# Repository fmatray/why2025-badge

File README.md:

# WHY2025 Badge

The Cyber Saiyan community designed and developed a special gadget to celebrate [WHY2025](https://www.cybersaiyan.it/why2025/)... You can get one of the 200 available badges at the [Cyber Saiyan Village](https://wiki.why2025.org/Village:Cyber_Saiyan) and start playing.

## Useful information:

* To play with and hack the badge, we recommend bringing a **USB Type‑C data cable**
* The badge is already flashed with the WHY2025 specific firmware
* We would greatly appreciate any improvements to the project and pull requests.
* Don't hesitate to come and visit us at the Cyber Saiyan Village if you need help
* **Bonus**: on [Day 2, Aug 9, 2025 at 16:00 in Cassiopeia](https://cfp.why2025.org/why2025/talk/3CSQRF/) we present the hardware design and the firmware during the talk "Summoning Shenron: Building the Cyber Saiyan Badge"

## Features

The badge has several simple features to enhance your Village experience:
* It is designed to recall the dragon spheres (maybe you will be able to summon Shenron...)
* The core is a low-power **ESP32-C3** SoC
   * Integrates a 32-bit single-core RISC-V microcontroller with a maximum clock speed of 160 MHz
   * 400 KB of internal RAM and 4MB flash
   * Wi-Fi and Bluetooth 5 (LE)
   * 16 programmable GPIOs
* In the front there are 7 RGB leds
* In the back you have  
   * A 2.8'' TFT screen 
   * A LiPo battery, connectors and power switch
   * A reset button
   * 2 Dial Wheel Switch
   * 8 connectors for configurable GPIOs and expansions

## Interaction

Once powered on, the badge is assigned an ID from 1 to 7 and begins advertising itself via BLE.

**Change Screens**: **Long-press** (at least 1 second) either Dial Wheel Switch.

You can interact with the screen by short pressing (up or down) one of the two Dial Wheel Switch.

## Screens

### First screen

The Cyber Saiyan WHY2025 logo

### Second screen

A BADGE with a name, an organization, a job and a message... and a secret identity ;-)

### Thrid screen

The Cyber Saiyan Village schedule. Use the 5th screen to update it.

### Fourth Screen

The badge radar, showing nearby badges in a Dragon Ball style.

### Fifth screen

The badge's list, you can see all the badges around in a table view

### Sixt screen

The Wi-Fi functionalities

#### TURN ON AP

Start the AP mode (move up the Dial Wheel Switch) and connect from your PC/phone to the badge AP using SSID and PASS shown; after that you can navigate to `http://192.168.4.1` in order to explore more functionalities (hey Harry, can you play tetris?) and change configurations (`saiyan` is the pwd)

#### SYNC SCHEDULE

Start the SYNC mode (move down the Dial Wheel Switch) in order to update the Village schedule; the badge connects to WHY2025 open wi-fi to download the updated schedule from Cyber Saiyan website

### Seventh Screen
Have fun while playing Snake! 🐍

## Characteristics

The ESP32-C3 chip is the MCU at the core of the WHY2025 Badge, it integrates multiple peripherals to enable communication with the outside world.
The number of available pins is limited to keep the chip package size small. To route all the incoming and outgoing signals a set of software programmable registers controls the pin multiplexer.

### Peripheral Interfaces
There are 16 programmable GPIO pins available for:
* Digital interfaces
   * 3 SPI
   * 2 UART
   * I2C
   * I2S
   * Remote control peripheral, with 2 transmit channels and 2 receive channels
   * LED PWM controller, with up to 6 channels
   * Full-speed USB Serial/JTAG controller
   * General DMA controller (GDMA), with 3 transmit channels and 3 receive channels
   * TWAI® controller compatible with ISO 11898-1 (CAN Specification 2.0)
* Analog interfaces
   * 2 SAR ADCs (12-bit), up to 6 channels
   * Temperature sensor

### Devices on board
The WHY2025 Badge is equipped with a 2.8 inch TFT color LCD screen with 240 x 320 pixels, using the [ST7789](hardware/datasheet/ST7789V.pdf) display controller.
This display integrates a resistive touchscreen a white LEDs backlight and features an 18-pin standard FPC cable to interface the MCU with a 4-wire SPI bus.
___
The SPI bus signals are available on the connector labeled "SPI" at the top of the badge:
| pin  | function |
| :--- | :------: |
| 1    |   GND    |
| 2    |   MOSI   |
| 3    |    CS    |
| 4    |    DC    |
| 5    |   CLK    |
| 6    |   MISO   |

___
The current firmware version does not support touchscreen functionality, but the Badge still features the [TSC2007](hardware/datasheet/tsc2007.pdf) I2C Resistive Touch Screen Controller.

The front RGB LEDs are intelligent, individually addressable [WS2812B](hardware/datasheet/WS2812B.pdf) chips that communicate with each other and the microcontroller via a single data line. The data transfer protocol uses a single NZR communication mode. The signal from the DOUT port of the last LED on the badge is available on the "1W" pin of the connector, labeled "I2C."
___
The I2C bus signals are available on the connector labeled "I2C" at the top of the badge:
| pin  | function |
| :--- | :------: |
| 1    |   GND    |
| 2    |   SCL    |
| 3    |   SDA    |
| 4    |    1W    |
___
The display backlight is controlled by 4 pins on the [AW9523B](hardware/datasheet/AW9523.pdf) LED driver and GPIO controller with I2C interface while the other 12 pins on the I/O ports can be configured as LED drive mode or GPIO mode and are available on the connector labeled "RGB*".
___
The I/O signals from AW9523B are available on the connector labeled "RGB*" at the left of the badge:
| RGB0 | function |
| :--- | :------: |
| 1    |   GND    |
| 2    |   P0_0   |
| 3    |   P0_1   |
| 4    |   P0_2   |

| RGB1 | function |
| :--- | :------: |
| 1    |   GND    |
| 2    |   P0_3   |
| 3    |   P0_4   |
| 4    |   P0_5   |

| RGB2 | function |
| :--- | :------: |
| 1    |   GND    |
| 2    |   P0_6   |
| 3    |   P0_7   |
| 4    |   P1_4   |

| RGB3 | function |
| :--- | :------: |
| 1    |   GND    |
| 2    |   P1_5   |
| 3    |   P1_6   |
| 4    |   P1_7   |
___

The badge's main input interface consists of two **Dial Wheel Switches**. These switches can be rotated up or down for short and long presses to navigate and interact with the UI.
Pressing the center of the left switch results in the same effect as rotating the wheel UP, while pressing the center of the right switch results in the same effect as rotating the wheel DOWN.

Note: 
push the left switch (or rotating the wheel UP) during boot to put the MCU in Joint Download Boot mode to download binary files into flash using UART0 or USB interface. To reset/restart the MCU push the micro switch labeled "RST" on the top left of the badege.

During the boot process, the messages by the ROM code can be printed to (Default) UART0 and USB Serial/JTAG controller. 
___
The UART interface and the Strapping (button pin) signals are available on the connector labeled "RS232" at the top of the badge:
| pin  | function |
| :--- | :------: |
| 1    |   GND    |
| 2    |    TX    |
| 3    |    RX    |
| 4    | button B |
| 5    | button A |

___

The USB-C connector's D+/D- pins are connected to the default USB Serial/JTAG Controller and the USB power is routed to the LiPo battery charger and the voltage regulators.

There is the [MT3608](hardware/datasheet/MT3608B.pdf) step-up converter intended for power the WS2812 with up to 5V and the [MT3410LB](hardware/datasheet/MT3410LB-N.pdf) step-down DC-DC 3.3V regulator, capable of delivering up to 1.3A output current to the MCU and all the other IC.

In case of low power and low noise applications it's possible to disable the MT3410LB by removing two 0 ohm resistors labeled SW_ON/SW_OUT and enable the [RT9080](hardware/datasheet/RT9080-33.pdf) low-dropout (LDO) 3.3 voltage regulator by shorting two resistors pads labeled LDO_ON/LDO_OUT
___
The power lines are available on the connector labeled "POW" at the top of the badge:
| pin  | function |
| :--- | :------: |
| 1    |   GND    |
| 2    |  +3.3V   |
| 3    |  +4.75V  |
___

The battery is charged using a [TP4054](hardware/datasheet/TP4054.pdf) single-charge LiPo charger with a constant current/voltage algorithm and a [DW01](hardware/datasheet/dw01a.pdf) protection IC designed to protect the battery from damage due to over-discharge and/or over-current. The charging circuit and voltage regulators are always powered by the USB port. A toggle switch for turning the badge on and off via the battery is located on the bottom of the badge.

# Toolchain setup

## Prepare the environment 

### Visual Studio Code (VSCode)
Install Visual Studio Code as development environment:

* https://code.visualstudio.com/ - follow instructions there, if you don't have vscode yet.

### PlatformIO (PIO) extension
Install PlatformIO extension on Visual Studio Code:

* [Installation](http://docs.platformio.org/page/ide/vscode.html)
* [Quick Start](http://docs.platformio.org/page/ide/vscode.html#quick-start)
* [User Guide](http://docs.platformio.org/page/ide/vscode.html#user-guide)

Please follow to the official documentation [PlatformIO IDE for VSCode](http://docs.platformio.org/page/ide/vscode.html).

## Setup the project

* Git clone this repository and open it on VSCode

If you get a `No module named pkg_resources` error, open the PlatformIO Core CLI and run:
   * `pip install setuptools`

## Build www data (Linux)

* Prerequisites:
   * Install Node.js and NPM
* Use NPM to Install required Packages:
   * `npm install node-minify node-sass`

* `./www-build.sh`

## Build www data (Docker)

* Install docker
* `docker build --pull --rm -f "Dockerfile" -t why2025badge:latest "."`
* (Bash) `docker run -it -v $(pwd)/public:/public -v $(pwd)/data/www:/output why2025badge`
* (Powershell) `docker run -it -v ${PWD}/public:/public -v ${PWD}/data/www:/output why2025badge`
   
## Build/Upload Filesystem

In order to upload the filesystem to the badge you need to plugin the badge using USB.
In the "Project Tasks" view of PIO navigate to:

* `WHY2025-Bagde`
   * `Platform`
      * `Build Filesystem Image`
      * `Upload Filesystem Image`

## Build/Upload Firmware
In order to upload the firmware to the badge you need to plugin the badge using USB.
In the "Project Tasks" view of PIO navigate to:

* `WHY2025-Bagde`
   * `General`
      * `Build`
      * `Upload`

## Flash Erase 
After a flash erase, you'll need to upload the firmaware AND upload data files with "pio run -t uploadfs".

# Known Issues
Check [GitHub issue tracker](https://github.com/CyberSaiyanIT/why2025-badge/issues)

# Misc

## Wi-Fi SSID name lenght limit

The Wi-Fi SSID for connecting to an external Access Point (AP) is limited to **20 characters**.

## Use a different logo image

* Convert the BMP/JPG/PNG/SVG file to a C array. You can do this using an [online image converter](https://lvgl.io/tools/imageconverter): use LVGL v8, CF_TRUE_COLOR_ALPHA as color format and and C array as output
* adjust [main/badge/common/img_logo.c](main/badge/common/img_logo.c) file

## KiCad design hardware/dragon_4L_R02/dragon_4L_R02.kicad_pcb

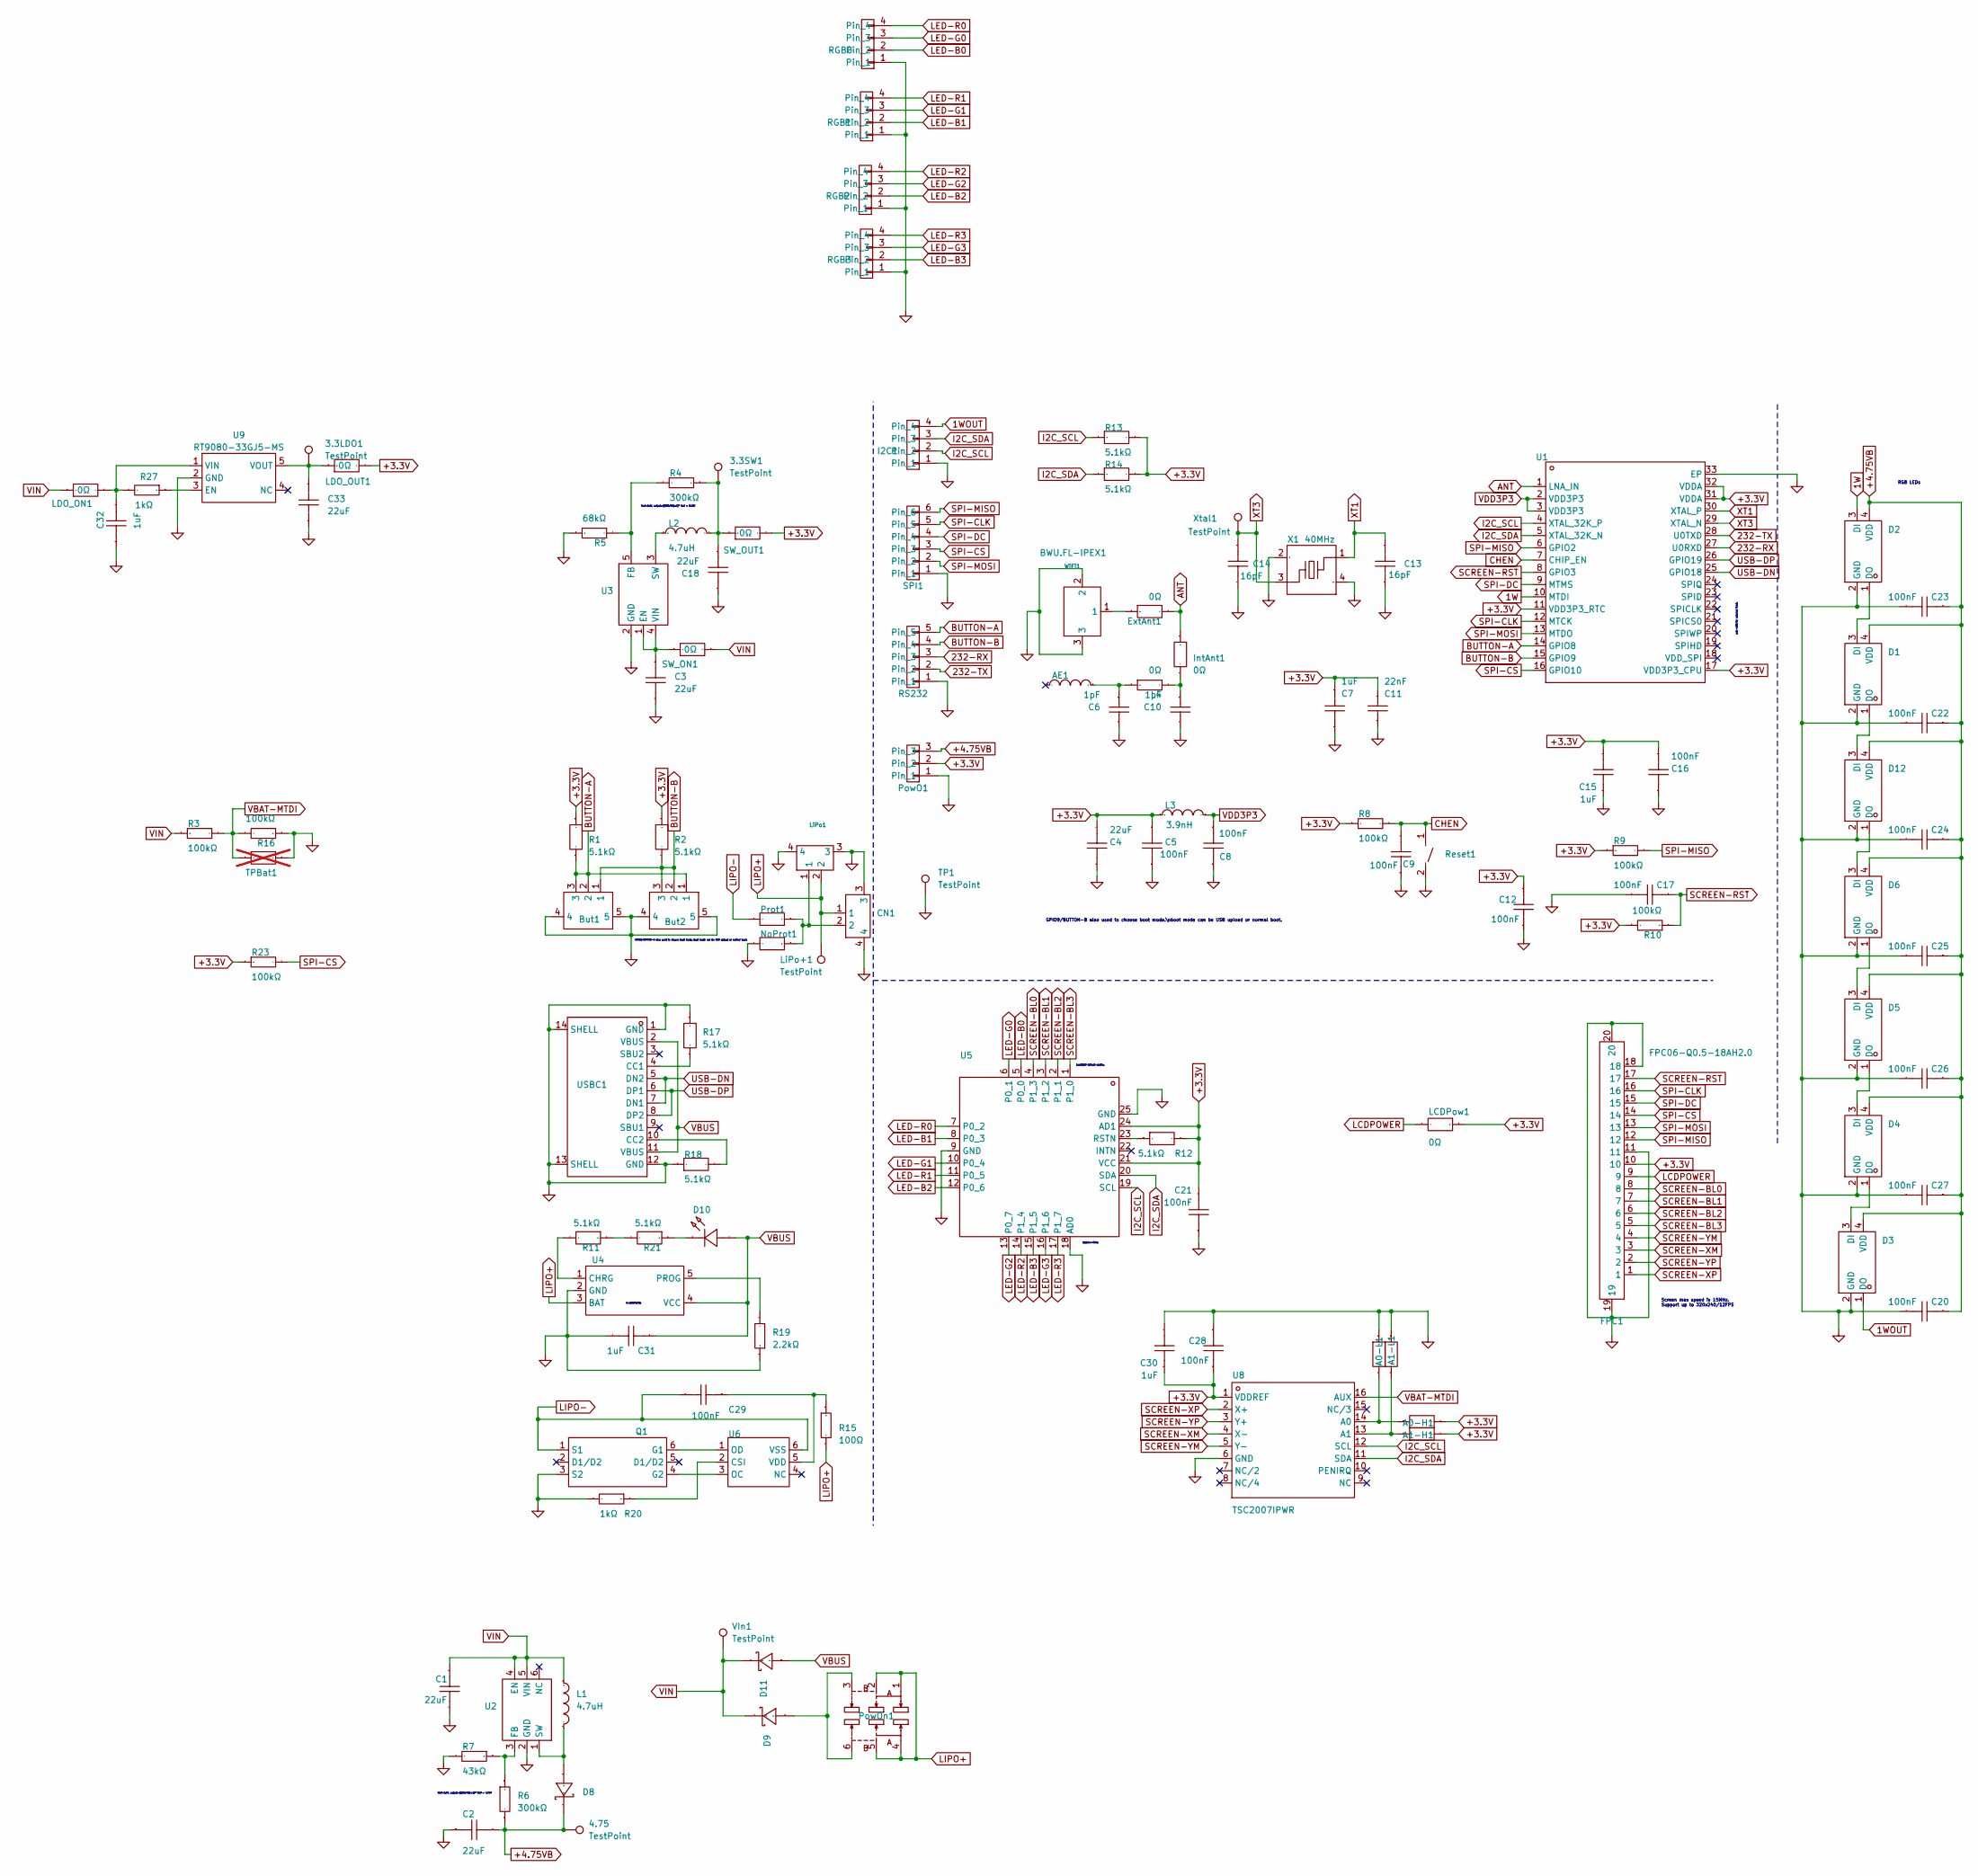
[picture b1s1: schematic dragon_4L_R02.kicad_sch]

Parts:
3.3LDO1, 3.3SW1, 4.75: TestPoint; TestPoint_Pad_D1.5mm
A0-H1, A0-L1, A1-H1, A1-L1: 0Ω; R0805; Manufacturer Part FRC0805P000 TS; LCSC Part Name 0Ω ±5% 125mW 厚膜电阻
AE1: AN9520-245; ANT-SMD_L9.5-W2.1; Manufacturer Part AN9520-245; LCSC Part Name AN9520-245
But1, But2: QS-301-AGS5P; SW-SMD_QS-301-AGS5P; Manufacturer Part QS-301-AGS5P; LCSC Part Name 三脚 大头拨轮多功能开关 MP3/MP4换曲按键
C1, C2, C3, C4, C18, C33: 22uF; C0603; Manufacturer Part CL10A226MQ8NRNC; LCSC Part Name 22uF ±20% 6.3V
C5, C8, C9, C12, C16, C17, C20, C21, C22, C23, C24, C25, C26, C27, C28, C29: 100nF; C0603; Manufacturer Part FCC0603B104K500CT; LCSC Part Name 100nF ±10% 50V
C6, C10: 1pF; C0402; Manufacturer Part GJM1555C1H1R0WB01D; LCSC Part Name 1pF 50V ±0.05pF
C7, C15, C30, C31, C32: 1uF; C0603; Manufacturer Part CGA0603X5R105K160JT; LCSC Part Name 1uF ±10% 16V
C11: 22nF; C0402; Manufacturer Part CC0402KRX7R9BB223; LCSC Part Name 22nF ±10% 50V
C13, C14: 16pF; C0603; Manufacturer Part CC0603JRNPO9BN160; LCSC Part Name 16pF ±5% 50V
CN1: HCZZ0001-2; CONN-SMD_2P-P1.25_HC_HCZZ0001-2; Manufacturer Part HCZZ0001-2; LCSC Part Name 米色 1x2P 间距:1.25mm 卧贴 系列:PicoBlade(MX 1.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
D1, D2, D3, D4, D5, D6, D12: WS2812B-2020; LED-SMD_4P-L2.0-W2.0-TL_WS2812B-2020; Manufacturer Part WS2812B-2020; LCSC Part Name RGB三色
D8, D9, D11: CRS08(TE85L,Q,M); SOD-123_L2.8-W1.8-LS3.7-FD; Manufacturer Part CRS08(TE85L,Q,M); LCSC Part Name 电压:30V 电流:1.5A
D10: XL-1005UGC; LED0402-RD_GREEN; Manufacturer Part XL-1005UGC; LCSC Part Name XL-1005UGC
ExtAnt1: 0Ω; R0805; Manufacturer Part FRC0805P000 TS; LCSC Part Name 0Ω ±5% 125mW 厚膜电阻
FPC1: FPC06-Q0.5-18AH2.0; FPC-SMD_18P-P0.50_FPC06-Q0.5-18AH2.0; Manufacturer Part FPC06-Q0.5-18AH2.0; LCSC Part Name 间距:0.5mm P数:18P 翻盖式 下接
I2C1: HCZZ0015-4; CONN-SMD_4P-P1.25_HCZZ0015-4; Manufacturer Part HCZZ0015-4; LCSC Part Name 米色 1x4P 间距:1.25mm 立贴闭口不加盖 系列:PicoBlade(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
IntAnt1: 0Ω; R0805; Manufacturer Part FRC0805P000 TS; LCSC Part Name 0Ω ±5% 125mW 厚膜电阻
L1, L2: 4.7uH; IND-SMD_L4.0-W4.0_FNR40XXS; Manufacturer Part FNR4030S4R7MT; LCSC Part Name 4.7uH ±20% 3.2A
L3: 3.9nH; IND-SMD_L1.0-W0.5-2; Manufacturer Part LQW15AN3N9B00D; LCSC Part Name 3.9nH
L4: 0Ω; R0402; Manufacturer Part 0402WGF0000TCE; LCSC Part Name 0Ω ±1% 62.5mW 厚膜电阻
LCDPow1: 0Ω; R0805; Manufacturer Part FRC0805P000 TS; LCSC Part Name 0Ω ±5% 125mW 厚膜电阻
LDO_ON1: 0Ω; R0805; Manufacturer Part FRC0805P000 TS; LCSC Part Name 0Ω ±5% 125mW 厚膜电阻
LDO_OUT1: 0Ω; R0805; Manufacturer Part FRC0805P000 TS; LCSC Part Name 0Ω ±5% 125mW 厚膜电阻
LiPo1: BX-PH2.0-2PWT; CONN-SMD_2P-P2.00_BX-PH2.0-2PWT; Manufacturer Part BX-PH2.0-2PWT; LCSC Part Name 1x2P 间距:2mm 卧贴 系列:PH
LiPo+1: TestPoint; TestPoint_Pad_D1.5mm
NoProt1: 0Ω; R0805; Manufacturer Part FRC0805P000 TS; LCSC Part Name 0Ω ±5% 125mW 厚膜电阻
PowO1: HCZZ0015-3; CONN-SMD_3P-P1.25-L3.3-W8.8; Manufacturer Part HCZZ0015-3; LCSC Part Name 米色 1x3P 间距:1.25mm 立贴闭口不加盖 系列:PicoBlade(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
PowOn1: MST22D18G2 125; SW-SMD_MST22D18G2; Manufacturer Part MST22D18G2 125; LCSC Part Name 拨动开关/两档立式 6脚贴片 柄长2.0mm 大六立贴 9.1*3.5mm
Prot1: 0Ω; R0805; Manufacturer Part FRC0805P000 TS; LCSC Part Name 0Ω ±5% 125mW 厚膜电阻
Q1: HJ8205; SOT-23-6_L2.9-W1.6-P0.95-LS2.8-BR; Manufacturer Part HJ8205; LCSC Part Name 1个N沟道 耐压:20V 电流:4.3A
R1, R2, R11, R12, R13, R14, R17, R18, R21: 5.1kΩ; R0603; Manufacturer Part SCR0603F5K1; LCSC Part Name 厚膜电阻 5.1kΩ ±1% 100mW
R3, R8, R9, R10, R16, R23: 100kΩ; R0603; Manufacturer Part RC0603FR-07100KL; LCSC Part Name 厚膜电阻 100kΩ ±1% 100mW
R4, R6: 300kΩ; R0402; Manufacturer Part RC0402FR-07300KL; LCSC Part Name 厚膜电阻 300kΩ ±1% 62.5mW
R5: 68kΩ; R0402; Manufacturer Part RC0402FR-0768KL; LCSC Part Name 厚膜电阻 68kΩ ±1% 62.5mW
R7: 43kΩ; R0402; Manufacturer Part RC0402FR-0743KL; LCSC Part Name 厚膜电阻 43kΩ ±1% 62.5mW
R15: 100Ω; R0402; Manufacturer Part 0402WGF1000TCE; LCSC Part Name 100Ω ±1% 62.5mW 厚膜电阻
R19: 2.2kΩ; R0402; Manufacturer Part RMC04022.2K1%N; LCSC Part Name 2.2kΩ ±1% 62.5mW
R20, R27: 1kΩ; R0402; Manufacturer Part 0402WGF1001TCE; LCSC Part Name 1kΩ ±1% 62.5mW 厚膜电阻
RGB0, RGB1, RGB2, RGB3: HCZZ0015-4; CONN-SMD_4P-P1.25_HCZZ0015-4; Manufacturer Part HCZZ0015-4; LCSC Part Name 米色 1x4P 间距:1.25mm 立贴闭口不加盖 系列:PicoBlade(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
RS232: HCZZ0015-5; CONN-SMD_5P-P1.25_HCZZ0015-5; Manufacturer Part HCZZ0015-5; LCSC Part Name 米色 1x5P 间距:1.25mm 立贴闭口不加盖 系列:PicoBlade(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
Reset1: TSB008A2526A; SW-SMD_L6.0-W3.5-LS8.0; Manufacturer Part TSB008A2526A; LCSC Part Name 新一型3*6*2.5H-YL 260gf 白钮
SPI1: HCZZ0015-6; CONN-SMD_6P-P1.25_HCZZ0015-6; Manufacturer Part HCZZ0015-6; LCSC Part Name 米色 1x6P 间距:1.25mm 立贴闭口不加盖 系列:PicoBlade(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
SW_ON1: 0Ω; R0805; Manufacturer Part FRC0805P000 TS; LCSC Part Name 0Ω ±5% 125mW 厚膜电阻
SW_OUT1: 0Ω; R0805; Manufacturer Part FRC0805P000 TS; LCSC Part Name 0Ω ±5% 125mW 厚膜电阻
TP1: TestPoint; MountingHole_4.5mm_Pad_Via
TPBat1: 0Ω; R0805; Manufacturer Part FRC0805P000 TS; LCSC Part Name 0Ω ±5% 125mW 厚膜电阻; not fitted
U1: ESP32-C3FH4; QFN-32_L5.0-W5.0-P0.50-TL-EP3.7; Manufacturer Part ESP32-C3FH4; LCSC Part Name ESP32-C3FH4
U2: MT3608B; SOT-23-6_L2.9-W1.6-P0.95-LS2.8-BR; Manufacturer Part MT3608B; LCSC Part Name 高效1.2MHz升压转换器
U3: MT3410LB-N; SOT-23-5_L3.0-W1.5-P0.95-LS2.8-BL; Manufacturer Part MT3410LB-N; LCSC Part Name MT3410LB-N
U4: TP4054; SOT-23-5_L2.9-W1.6-P0.95-LS2.8-BR; Manufacturer Part TP4054; LCSC Part Name TP4054
U5: AW9523BTQR; VFQFPN-24_L4.0-W4.0-P0.50-BL-EP2.8; Manufacturer Part AW9523BTQR; LCSC Part Name AW9523B产品手册
U6: DW01A; SOT-23-6_L2.9-W1.6-P0.95-LS2.8-BL; Manufacturer Part DW01A; LCSC Part Name DW01A
U8: TSC2007IPWR; TSSOP-16_L5.0-W4.4-P0.65-LS6.4-BL; Manufacturer Part TSC2007IPWR; LCSC Part Name TSC2007 触摸屏控制器
U9: RT9080-33GJ5-MS; SOT-23-5_L2.9-W1.6-P0.95-LS2.8-BR; Manufacturer Part RT9080-33GJ5-MS; LCSC Part Name RT9080-33GJ5-MS
USBC1: TYPE-C 16PIN 2MD(073); USB-C-SMD_TYPE-C-6PIN-2MD-073; Manufacturer Part TYPE-C 16PIN 2MD(073); LCSC Part Name Type-C 母 卧贴
VIn1: TestPoint; TestPoint_Pad_D1.5mm
WiFi1: BWU.FL-IPEX1; IPEX-SMD_BWIPX-1-001E; Manufacturer Part BWU.FL-IPEX1; LCSC Part Name 内针 IPEX
X1: 40MHz; CRYSTAL-SMD_4P-L3.2-W2.5-BL; Manufacturer Part L327S400H11L; LCSC Part Name 40MHz ±10ppm 10pF
Xtal1: TestPoint; TestPoint_Pad_D1.5mm

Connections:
1W: D2.3 (DI), U1.10 (MTDI)
1WOUT: D3.1 (DO), I2C1.4
232-RX: RS232.3, U1.27 (U0RXD)
232-TX: RS232.2, U1.28 (U0TXD)
+3.3V: A0-H1.2, A1-H1.2, C4.2, C5.2, C7.1, C11.1, C12.1, C15.2, C16.2, C21.2, C28.2, C30.1, FPC1.10, L3.1, LCDPow1.1, LDO_OUT1.2, PowO1.2, R1.1, R2.1, R8.1, R9.1, R10.2, R12.2, R13.2, R14.2, R23.1, SW_OUT1.2, U1.11 (VDD3P3_RTC), U1.17 (VDD3P3_CPU), U1.31 (VDDA), U1.32 (VDDA), U5.21 (VCC), U5.24 (AD1), U8.1 (VDDREF)
+4.75VB: 4.75.1, C2.2, C20.1, C22.1, C23.1, C24.1, C25.1, C26.1, C27.1, D1.4 (VDD), D2.4 (VDD), D3.4 (VDD), D4.4 (VDD), D5.4 (VDD), D6.4 (VDD), D8.2 (K), D12.4 (VDD), PowO1.3, R6.2
ANT: ExtAnt1.2, IntAnt1.1, U1.1 (LNA_IN)
BUTTON-A: But1.2, But1.3, But2.1, R1.2, RS232.5, U1.14 (GPIO8)
BUTTON-B: But1.1, But2.2, But2.3, R2.2, RS232.4, U1.15 (GPIO9)
CHEN: C9.2, R8.2, Reset1.1, U1.7 (CHIP_EN)
I2C_SCL: I2C1.2, R13.1, U1.4 (XTAL_32K_P), U5.19 (SCL), U8.12 (SCL)
I2C_SDA: I2C1.3, R14.1, U1.5 (XTAL_32K_N), U5.20 (SDA), U8.11 (SDA)
LCDPOWER: FPC1.9, LCDPow1.2
LED-B0: RGB0.2, U5.5 (P0_0)
LED-B1: RGB1.2, U5.8 (P0_3)
LED-B2: RGB2.2, U5.12 (P0_6)
LED-B3: RGB3.2, U5.15 (P1_5)
LED-G0: RGB0.3, U5.6 (P0_1)
LED-G1: RGB1.3, U5.10 (P0_4)
LED-G2: RGB2.3, U5.13 (P0_7)
LED-G3: RGB3.3, U5.16 (P1_6)
LED-R0: RGB0.4, U5.7 (P0_2)
LED-R1: RGB1.4, U5.11 (P0_5)
LED-R2: RGB2.4, U5.14 (P1_4)
LED-R3: RGB3.4, U5.17 (P1_7)
LIPO+: CN1.1, LiPo1.2, LiPo+1.1, PowOn1.1, PowOn1.2, PowOn1.4, PowOn1.5, R15.2, U4.3 (BAT)
LIPO-: C29.2, Prot1.2, Q1.1 (S1), U6.6 (VSS)
unnamed: 3.3SW1.1, C18.1, L2.2, R4.1, SW_OUT1.1
unnamed: AE1.1, C6.1, L4.1
unnamed: C10.1, IntAnt1.2, L4.2
unnamed: CN1.2, LiPo1.1, NoProt1.1, Prot1.1
unnamed: D1.3 (DI), D2.1 (DO)
unnamed: D1.1 (DO), D12.3 (DI)
unnamed: D3.3 (DI), D4.1 (DO)
unnamed: D4.3 (DI), D5.1 (DO)
unnamed: D5.3 (DI), D6.1 (DO)
unnamed: D8.1 (A), L1.2, U2.1 (SW)
unnamed: D9.1 (A), PowOn1.3, PowOn1.6
unnamed: D10.1 (K), R21.1
unnamed: D6.3 (DI), D12.1 (DO)
unnamed: ExtAnt1.1, WiFi1.1
unnamed: Q1.6 (G1), U6.1 (OD)
unnamed: Q1.4 (G2), U6.3 (OC)
unnamed: R11.1, R21.2
unnamed: R6.1, R7.1, U2.3 (FB)
unnamed: C3.1, SW_ON1.1, U3.1 (EN), U3.4 (VIN)
unnamed: R4.2, R5.2, U3.5 (FB)
unnamed: L2.1, U3.3 (SW)
unnamed: R11.2, U4.1 (CHRG)
unnamed: R19.2, U4.5 (PROG)
unnamed: R12.1, U5.23 (RSTN)
unnamed: R20.1, U6.2 (CSI)
unnamed: C29.1, R15.1, U6.5 (VDD)
unnamed: A0-H1.1, A0-L1.2, U8.14 (A0)
unnamed: A1-H1.1, A1-L1.2, U8.13 (A1)
unnamed: R27.1, U9.3 (EN)
unnamed: C32.2, LDO_ON1.2, R27.2, U9.1 (VIN)
unnamed: 3.3LDO1.1, C33.2, LDO_OUT1.1, U9.5 (VOUT)
unnamed: R17.2, USBC1.4 (CC1)
unnamed: R18.2, USBC1.10 (CC2)
POWER_GND: A0-L1.1, A1-L1.1, But1.4, But1.5, But2.4, But2.5, C1.2, C2.1, C3.2, C4.1, C5.1, C6.2, C7.2, C8.1, C9.1, C10.2, C11.2, C12.2, C13.1, C14.2, C15.1, C16.1, C17.2, C18.2, C20.2, C21.1, C22.2, C23.2, C24.2, C25.2, C26.2, C27.2, C28.1, C30.2, C31.2, C32.1, C33.1, CN1.3, CN1.4, D1.2 (GND), D2.2 (GND), D3.2 (GND), D4.2 (GND), D5.2 (GND), D6.2 (GND), D12.2 (GND), FPC1.11, FPC1.18, FPC1.19, FPC1.20, I2C1.1, LiPo1.3, LiPo1.4, NoProt1.2, PowO1.1, Q1.3 (S2), R5.1, R7.2, R16.1, R17.1, R18.1, R19.1, R20.2, RGB0.1, RGB1.1, RGB2.1, RGB3.1, RS232.1, Reset1.2, SPI1.1, TP1.1, TPBat1.1, U1.33 (EP), U2.2 (GND), U3.2 (GND), U4.2 (GND), U5.9 (GND), U5.18 (AD0), U5.25 (GND), U8.6 (GND), U9.2 (GND), USBC1.1 (GND), USBC1.12 (GND), USBC1.13 (SHELL), USBC1.14 (SHELL), WiFi1.2, WiFi1.3, X1.2 (GND), X1.4 (GND)
SCREEN-BL0: FPC1.8, U5.4 (P1_3)
SCREEN-BL1: FPC1.7, U5.3 (P1_2)
SCREEN-BL2: FPC1.6, U5.2 (P1_1)
SCREEN-BL3: FPC1.5, U5.1 (P1_0)
SCREEN-RST: C17.1, FPC1.17, R10.1, U1.8 (GPIO3)
SCREEN-XM: FPC1.3, U8.4 (X-)
SCREEN-XP: FPC1.1, U8.2 (X+)
SCREEN-YM: FPC1.4, U8.5 (Y-)
SCREEN-YP: FPC1.2, U8.3 (Y+)
SPI-CLK: FPC1.16, SPI1.5, U1.12 (MTCK)
SPI-CS: FPC1.14, R23.2, SPI1.3, U1.16 (GPIO10)
SPI-DC: FPC1.15, SPI1.4, U1.9 (MTMS)
SPI-MISO: FPC1.12, R9.2, SPI1.6, U1.6 (GPIO2)
SPI-MOSI: FPC1.13, SPI1.2, U1.13 (MTDO)
USB-DN: U1.25 (GPIO18), USBC1.5 (DN2), USBC1.7 (DN1)
USB-DP: U1.26 (GPIO19), USBC1.6 (DP1), USBC1.8 (DP2)
VBAT-MTDI: R3.2, R16.2, TPBat1.2, U8.16 (AUX)
VBUS: C31.1, D10.2 (A), D11.1 (A), U4.4 (VCC), USBC1.2 (VBUS), USBC1.11 (VBUS)
VDD3P3: C8.2, L3.2, U1.2 (VDD3P3), U1.3 (VDD3P3)
VIN: C1.1, D9.2 (K), D11.2 (K), L1.1, LDO_ON1.1, R3.1, SW_ON1.2, U2.4 (EN), U2.5 (VIN), VIn1.1
XT1: C13.2, U1.30 (XTAL_P), X1.1
XT3: C14.1, U1.29 (XTAL_N), X1.3, Xtal1.1

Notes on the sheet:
only valid for external flash.
Vref=0.6V, output=((300/43)+1)* Vref = 4.78V
Vref=0.6V, output=((300/68)+1)* Vref = 3.25V
RGB LEDs
Ic=1000V/Rp
GPIO9/BUTTON-B also used to choose boot mode.\nboot mode can be USB upload or normal boot.
backlight default enable.
GPIO9/BUTTON-B also used to choose boot mode. boot mode can be USB upload or normal boot.
address=0x5a
Screen max speed is 15MHz. Support up to 320x240/12FPS

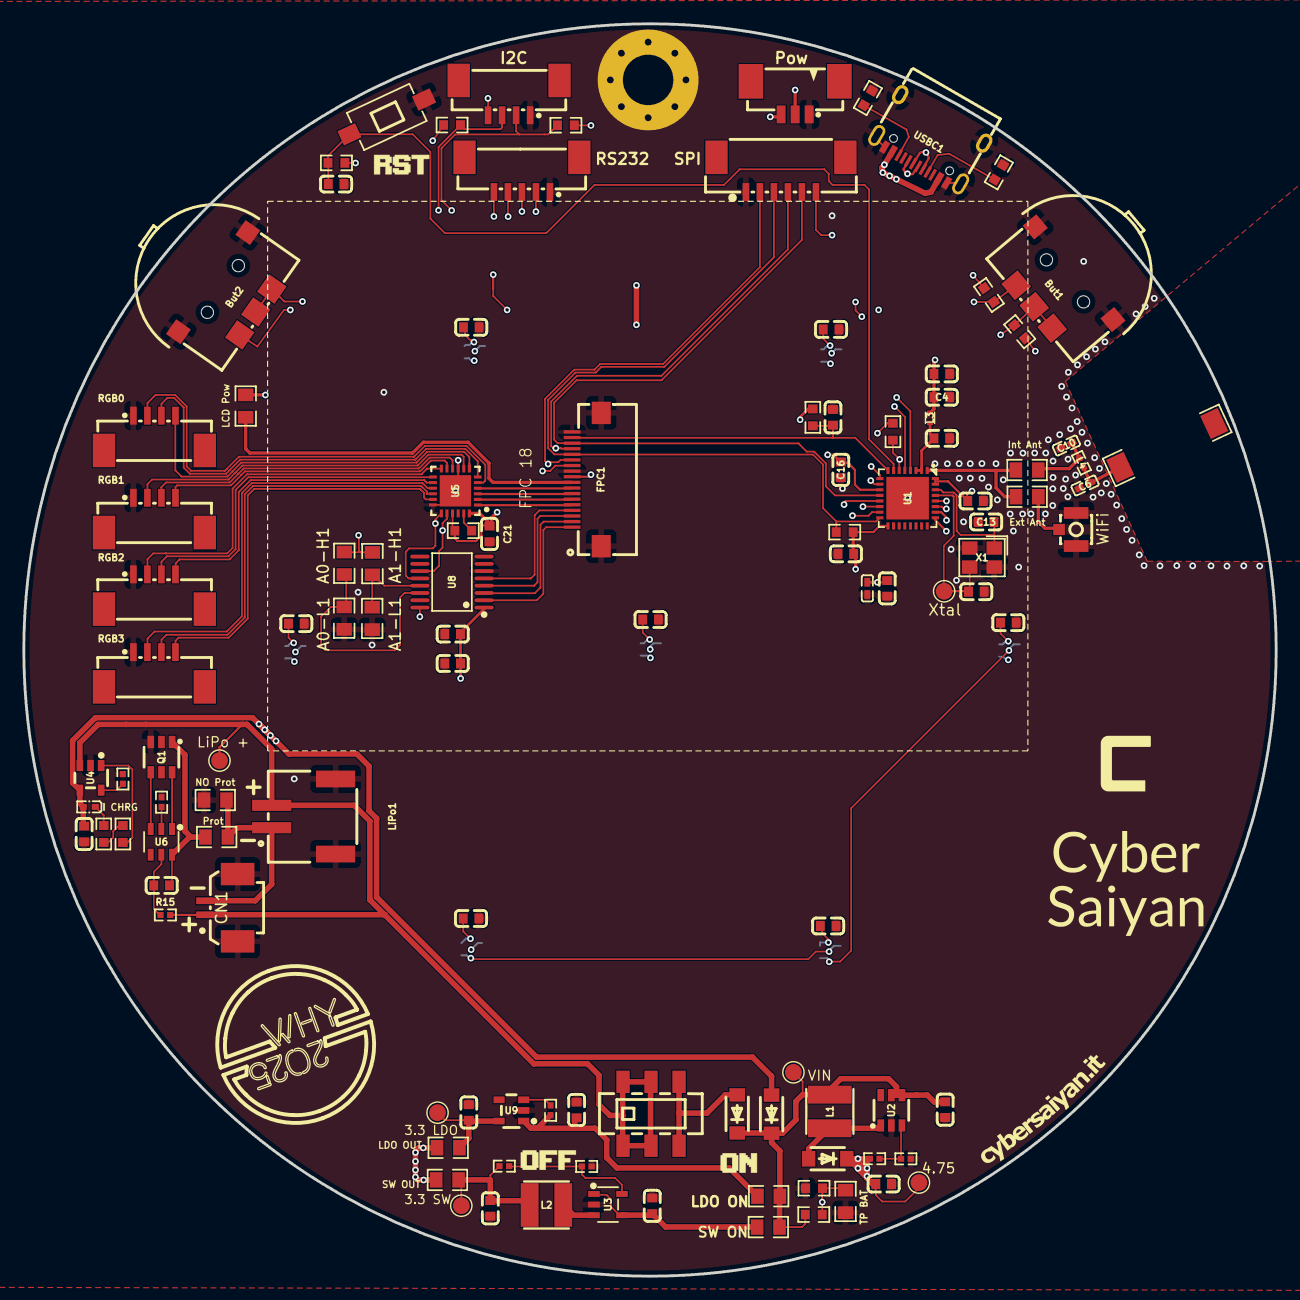
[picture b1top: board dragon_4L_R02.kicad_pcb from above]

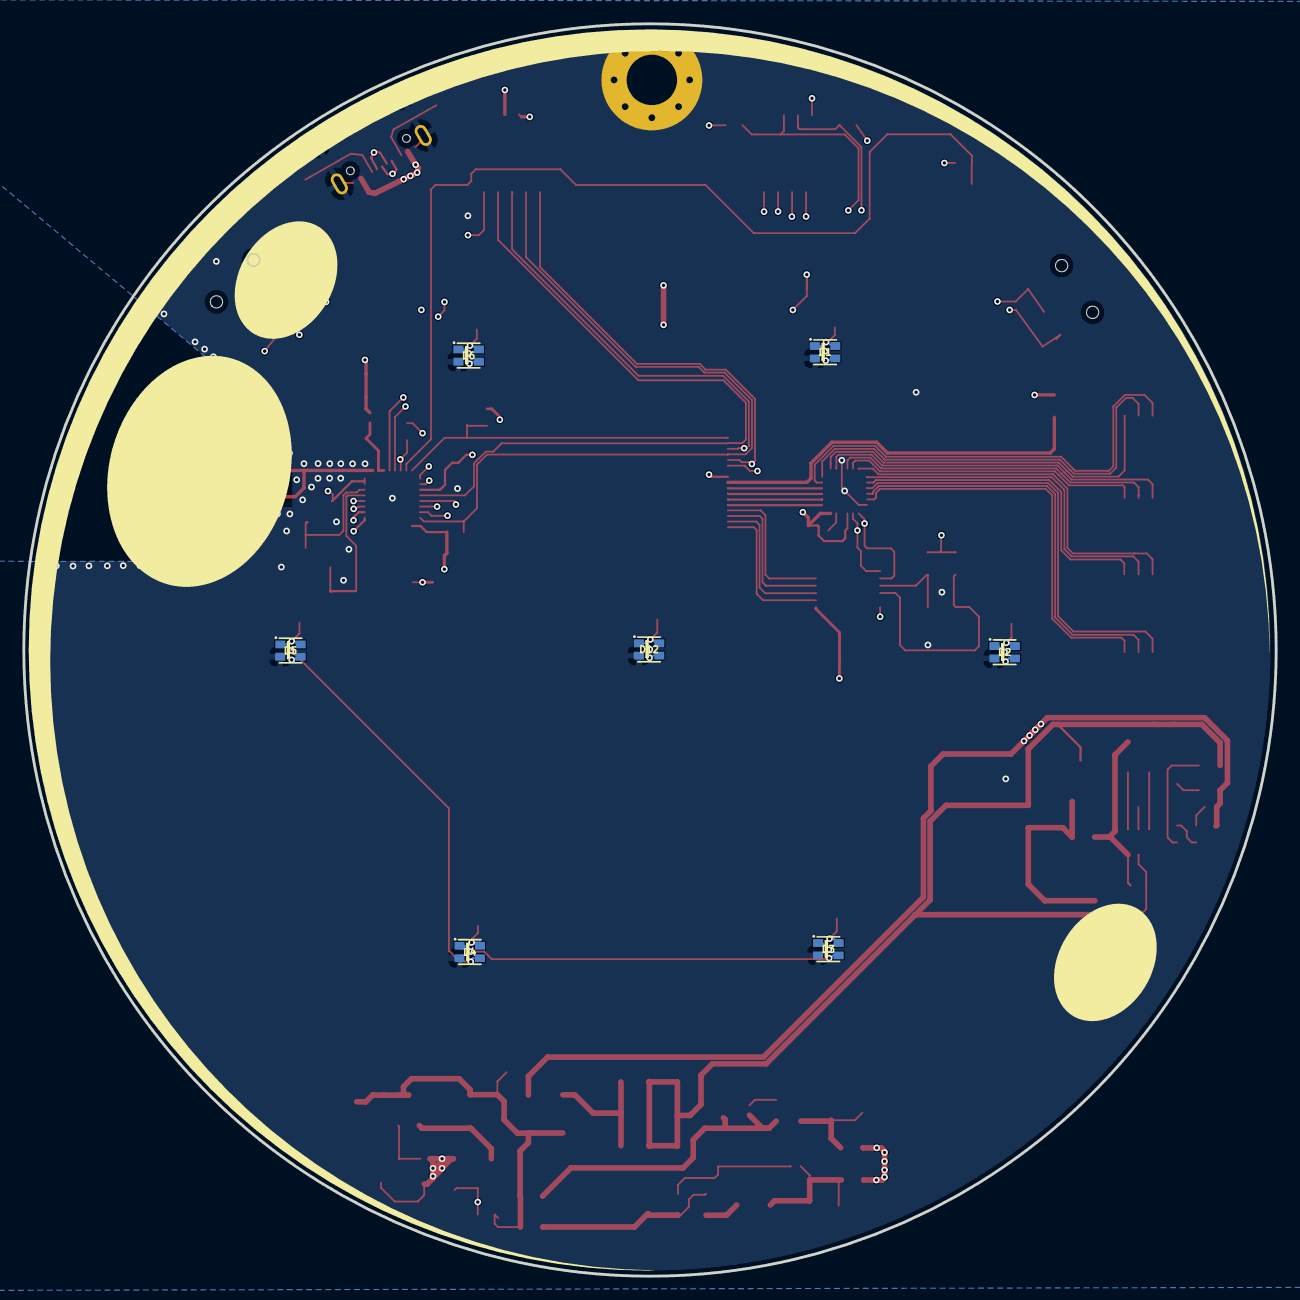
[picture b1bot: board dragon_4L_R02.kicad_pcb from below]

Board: 4 copper layers, 111.8 x 111.8 mm, 127 parts (9 on the bottom side), 83 nets.

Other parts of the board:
BALL**: Ball; RH_BALL
LOGO***: Logo; CS_LOGO
OFF**: Off; CS_OFF
ON**: On; CS_ON
RST**: Rst; CS_RST
STAR**: Star; CS_STAR
WEB**: Website; CS_WEBSITE
WHY***: LOGO; WHY_LOGO

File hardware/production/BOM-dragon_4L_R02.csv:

Comment,Designator,Footprint,LCSC,Quantity
22nF,C11,C0402,C107026,1
1kΩ,"R20,R27",R0402,C11702,2
68kΩ,R5,R0402,C137947,1
300kΩ,"R4,R6",R0402,C138011,2
"CRS08(TE85L,Q,M)","D11,D8,D9",SOD-123_L2.8-W1.8-LS3.7-FD,C141550,3
100kΩ,"R10,R16,R23,R3,R8,R9",R0603,C14675,6
AW9523BTQR,U5,VFQFPN-24_L4.0-W4.0-P0.50-BL-EP2.8,C148077,1
4.7uH,"L1,L2",IND-SMD_L4.0-W4.0_FNR40XXS,C167874,2
0Ω,L4,R0402,C17168,1
0Ω,"A0-L1,A1-L1,IntAnt1,LCDPow1,Prot1,SW_ON1,SW_OUT1",R0805,C17477,7
BX-PH2.0-2PWT,LiPo1,CONN-SMD_2P-P2.00_BX-PH2.0-2PWT,C18077890,1
43kΩ,R7,R0402,C185415,1
MT3608B,U2,SOT-23-6_L2.9-W1.6-P0.95-LS2.8-BR,C19189893,1
FPC06-Q0.5-18AH2.0,FPC1,FPC-SMD_18P-P0.50_FPC06-Q0.5-18AH2.0,C19267985,1
HJ8205,Q1,SOT-23-6_L2.9-W1.6-P0.95-LS2.8-BR,C20069150,1
100Ω,R15,R0402,C25076,1
TYPE-C 16PIN 2MD(073),USBC1,USB-C-SMD_TYPE-C-6PIN-2MD-073,C2765186,1
ESP32-C3FH4,U1,QFN-32_L5.0-W5.0-P0.50-TL-EP3.7,C2858491,1
TSB008A2526A,Reset1,SW-SMD_L6.0-W3.5-LS8.0,C2888456,1
MST22D18G2 125,PowOn1,SW-SMD_MST22D18G2,C2906280,1
DW01A,U6,SOT-23-6_L2.9-W1.6-P0.95-LS2.8-BL,C2927799,1
5.1kΩ,"R1,R11,R12,R13,R14,R17,R18,R2,R21",R0603,C3016319,9
2.2kΩ,R19,R0402,C325418,1
16pF,"C13,C14",C0603,C327125,2
TSC2007IPWR,U8,TSSOP-16_L5.0-W4.4-P0.65-LS6.4-BL,C38398,1
QS-301-AGS5P,"But1,But2",SW-SMD_QS-301-AGS5P,C42377853,2
MT3410LB-N,U3,SOT-23-5_L3.0-W1.5-P0.95-LS2.8-BL,C42420805,1
BWU.FL-IPEX1,WiFi1,IPEX-SMD_BWIPX-1-001E,C5137195,1
100nF,"C12,C16,C17,C20,C21,C22,C23,C24,C25,C26,C27,C28,C29,C5,C8,C9",C0603,C5137636,16
40MHz,X1,CRYSTAL-SMD_4P-L3.2-W2.5-BL,C5261245,1
TP4054,U4,SOT-23-5_L2.9-W1.6-P0.95-LS2.8-BR,C5381776,1
22uF,"C1,C18,C2,C3,C33,C4",C0603,C59461,6
1uF,"C15,C30,C31,C32,C7",C0603,C6119849,5
1pF,"C10,C6",C0402,C72134,2
HCZZ0001-2,CN1,CONN-SMD_2P-P1.25_HC_HCZZ0001-2,C7433453,1
HCZZ0015-3,PowO1,CONN-SMD_3P-P1.25-L3.3-W8.8,C7433469,1
HCZZ0015-4,"I2C1,RGB0,RGB1,RGB2,RGB3",CONN-SMD_4P-P1.25_HCZZ0015-4,C7433470,5
HCZZ0015-5,RS232,CONN-SMD_5P-P1.25_HCZZ0015-5,C7433471,1
HCZZ0015-6,SPI1,CONN-SMD_6P-P1.25_HCZZ0015-6,C7433472,1
RT9080-33GJ5-MS,U9,SOT-23-5_L2.9-W1.6-P0.95-LS2.8-BR,C7528830,1
WS2812B-2020,"D1,D12,D2,D3,D4,D5,D6",LED-SMD_4P-L2.0-W2.0-TL_WS2812B-2020,C965555,7
XL-1005UGC,D10,LED0402-RD_GREEN,C965793,1
3.9nH,L3,IND-SMD_L1.0-W0.5-2,C98062,1
AN9520-245,AE1,ANT-SMD_L9.5-W2.1,C99665,1

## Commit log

2025-07-22 First commit for WHY2025 badge
2025-07-22 Add missing config file and update version
2025-07-22 Add vscode files too
2025-07-26 Amatriciana day set
2025-07-26 Fix wifi to connect to open wifi networks Configured connection to WHY2025-open network (see https://wiki.why2025.org/Network#Wireless)
2025-07-29 Update badge images Add the real badge image too
2025-07-29 Improve README Add images and rephrase a lot
2025-07-29 Minor fix to sections
2025-07-29 Add webserver screenshot and some info
2025-08-02 Update README.md for issue tracking
2025-08-04 Update village schedule as of Aug 4th
2025-08-04 Add rainbow easter egg Sequence to trigger rainbow lights
2025-08-04 Fix missing null-terminating the string In the load_schedule_from_file function, after allocating memory with malloc(file_size + 1) and reading the file content with fread(), the function is missing 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
    The buffer is not being null-terminated, which means when the JSON string is sent to the client, it may contain garbage data at the end, making it invalid JSON that cannot be parsed by the browser.
2025-08-04 Fix SSL memory allocation error (MBEDTLS_ERR_SSL_ALLOC_FAILED)
    - Reduce SSL buffer sizes from 16KB/4KB to 8KB/2KB
    - Enable dynamic SSL buffer allocation
    - Add memory checks before attempting SSL connections
    - Limit HTTP client buffer sizes
    - Improve error handling and cleanup
    - Add heap memory logging for debugging
2025-08-04 Git rev and sdk updates
2025-08-05 Fix mobile radar display: make Dragon Ball radar responsive
    - Add mobile-responsive CSS for radar display on phones
    - Reduce radar size from 360px to 280px on tablets (≤760px)
    - Further reduce to 240px on small phones (≤480px)
    - Add proper centering with auto margins and text-align center
    - Update HTML responsive classes for better mobile layout
    - Maintain Dragon Ball radar styling and animations
2025-08-05 Fix LED collision between easter eggs and normal flashing
    - Add easter_egg_active flag to prevent LED task interference
    - Block normal LED flashing during rainbow() and set_completed() execution
    - Add set_easter_egg_active() function to control the blocking mechanism
    - Ensure easter eggs run without interruption from the LED task
    - LED task now checks easter_egg_active flag and waits when easter eggs are running
    Closes #13
2025-08-06 Fix crontab visualization by skipping empty table cells
    - Modified generate_table function in helpers.js to check if field values exist and are not empty before creating table cells
    - Prevents broken visualization when schedule.json contains empty duration fields
    - Only creates table rows for fields that have actual content
    - Fixes display issues in the schedule tab (crontab -l section)
2025-08-06 Prepare for release 1.0
2025-08-09 Fix backlight Enhance the backlight brightness
2025-08-19 Add a new "person" screen
    modified: data/default.json
    modified: data/www/index.html
    modified: data/www/js/client.js
    modified: data/www/js/index.js
    modified: main/badge/badge.c
    modified: main/badge/badge.h
2025-08-19 Debuging and refactoring
    modified: data/default.json
    modified: main/badge/httpd.c
    modified: main/badge/httpd.h
    modified: main/badge/ui.c
    modified: main/badge/ui.h
2025-08-20 Small color debug modified: data/default.json
2025-08-20 Add secret identity
    modified: README.md
    modified: data/default.json
    modified: data/www/index.html
    modified: data/www/js/client.js
    modified: data/www/js/index.js
    modified: main/badge/badge.c
2025-08-21 - Code refactoring - And social energy gauge
    modified: README.md
    modified: components/lvgl/src/lv_widgets/lv_gauge.c
    modified: main/badge/badge.c
    modified: main/badge/badge.h
    modified: main/badge/httpd.c
    modified: main/badge/ui.c
2025-08-21 cleaning modified: .vscode/settings.json modified: main/badge/ui.c
2025-08-23 First compilation with 8.4.0
2025-08-23 Tables debugging modified: main/badge/ui.c
2025-08-24 split ui.c and ui.h Split ui.c and ui.h in several files to improve readability Code refactoring
    modified: main/badge/badge.h
    modified: main/badge/httpd.h
    deleted: main/badge/snake.c
    modified: main/badge/sync.h
    deleted: main/badge/ui.c
    deleted: main/badge/ui.h
2025-08-30 version update. lcd_init() still not working.
2025-08-30 add missong files
2025-08-30 lv_conf.h debug
2025-08-30 Debug screen init
2025-08-30 version update
2025-08-31 firest version of lcd.c
2025-09-01 try to update espressif IDF
